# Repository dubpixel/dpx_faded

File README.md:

<!-- Improved compatibility of back to top link: See: https://github.com/othneildrew/Best-README-Template/pull/73 -->

<!--  *** Thanks for checking out the Best-README-Template. If you have a suggestion that would make this better, please fork the repo and create a pull request or simply open an issue with the tag "enhancement". Don't forget to give the project a star! Thanks again! Now go create something AMAZING! :D -->

<!-- /// d   u   b   p   i   x   e   l  ---  f   o   r   k   ////--v0.5.0 -->
<!--this has additionally been modifed by @dubpixel for hardware use -->
<!--search dpx_faded.. search & replace is COMMAND OPTION F -->

<!--todo add small product image thats not in a details tag -->
<!--igure out how to get the details tag to properly render in jekyll for gihub pages.-->

<!-- PROJECT SHIELDS -->
<!--
*** I'm using markdown "reference style" links for readability.
*** Reference links are enclosed in brackets [ ] instead of parentheses ( ).
*** See the bottom of this document for the declaration of the reference variables
*** for contributors-url, forks-url, etc. This is an optional, concise syntax you may use.
*** https://www.markdownguide.org/basic-syntax/#reference-style-links
***
-->
[![Contributors][contributors-shield]][contributors-url]
[![Forks][forks-shield]][forks-url]
[![Stargazers][stars-shield]][stars-url]
[![Issues][issues-shield]][issues-url]
[![CERN-OHL-S-2.0][license-shield]][license-url]
[![LinkedIn][linkedin-shield]][linkedin-url]

<!-- PROJECT LOGO -->
<br />
<div align="center">

<h1 align="center">dpx_faded</h1>
<h3 align="center"><i>because whats life without fader?</i></h3>
<br />
  <p align="center">
    ...a motorized fader breakout inspired by the FADER_4. Since there were only gerbers that didnt seem to match any faders available easily  - i re made a KiCAD project based on the 1.8 board revision. Included here for quick reference is a VScode migrated FADER_X firmware distro... soon to be migrated to its own _genuine_ fork.
        <br />
     »  
     <a href="https://github.com/dubpixel/dpx_faded/tree/main/"><strong>Project Here!</strong></a>
     »  
    <a href="https://github.com/dubpixel/dpx_faded/tree/main/hardware/src/dpx_faded/bom"><strong>BOM Here!</strong></a>
     » 
    <a href="https://dubpixel.github.io/dpx_faded/ibom/index.html"><strong>Interactive BOM Here!</strong></a>
     <br />
    <a href="https://github.com/dubpixel/dpx_faded/issues/new?labels=bug&template=bug-report---.md">Report Bug</a>
    ·
    <a href="https://github.com/dubpixel/dpx_faded/issues/new?labels=enhancement&template=feature-request---.md">Request Feature</a>
    </p>
</div>
   <br />
<!-- TABLE OF CONTENTS -->
<details>
<summary><h3>Table of Content</h3></summary>
<ol>
    <li>
      <a href="#about-the-project">About The Project</a>
      <ul>
        <li><a href="#built-with">Built With</a></li>
      </ul>
    </li>
    <li>
      <a href="#getting-started">Getting Started</a>
      <ul>
        <li><a href="#prerequisites">Prerequisites</a></li>
        <li><a href="#installation">Installation</a></li>
      </ul>
    </li>
    <li><a href="#usage">Usage</a></li>    
    <li><a href="#reflection">Reflection</a></li>
    <li><a href="#roadmap">Roadmap</a></li>
    <li><a href="#contributing">Contributing</a></li>
    <li><a href="#license">License</a></li>
    <li><a href="#contact">Contact</a></li>
    <li><a href="#acknowledgments">Acknowledgments</a></li>
</ol>
</details>
<br />
<!-- ABOUT THE PROJECT -->

<details>
<summary><h3>About The Project</h3></summary>
While the maker made the firmware open source, as well as the production gerber files - the cad files were not released in a malliable format, which doesnt allow further development of that hardware platform. (bummer). Since there is some community interest in the product, here we attempt to reverse engineer the FADE_4 as a proof of concept before continuing with development
</br>
author(s): // www.dubpixel.tv  - i@dubpixel.tv | other authors
</br>
<h3>Images</h3>

### FRONT
![FRONT][product-front]

### REAR 
![REAR][product-rear]

### FRONT Rendering
![FRONT][product-front-rendering]

### REAR Rendering
![REAR][product-rear-rendering]

### iBOM PCB Front
![iBOM Front][product-pcbFront]

### iBOM PCB Rear
![iBOM Front][product-pcbRear]

</details>

<p align="right">(<a href="#readme-top">back to top</a>)</p>

### Built With 
 * [![KiCad][KiCad.org]][KiCad-url]
 * [![Fusion360][Fusion-360]][Autodesk-url]
 * [![FastLed][FastLed.io]][FastLed-url]

<!--
  
 * [![Fusion360][Fusion-360]][Autodesk-url]
 * [![Next][Next.js]][Next-url]
 * [![React][React.js]][React-url]
 * [![Vue][Vue.js]][Vue-url]
 * [![Angular][Angular.io]][Angular-url]
 * [![Svelte][Svelte.dev]][Svelte-url]
 * [![Laravel][Laravel.com]][Laravel-url]
 * [![Bootstrap][Bootstrap.com]][Bootstrap-url]
 * [![JQuery][JQuery.com]][JQuery-url]
 
-->
<p align="right">(<a href="#readme-top">back to top</a>)</p>

<!-- GETTING STARTED -->
## Getting Started

### Prerequisites

### Installation

<!--
1. Download...
2. Enjoy.
3. Repeat as Needed! -->

<p align="right">(<a href="#readme-top">back to top</a>)</p>

<!-- USAGE EXAMPLES -->
## Usage

<!-- Use this space to show useful examples of how a project can be used. Additional screenshots, code examples and demos work well in this space. You may also link to more resources.

_For more examples, please refer to the [Documentation](https://example.com)_-->

<p align="right">(<a href="#readme-top">back to top</a>)</p>

## Reflection

* what did we learn? 
  - things take what they take. (good) things take more.
  - pinouts. always read the pinouts with parts on somoene elses BOM/hardware design
* what do we like/hate?
  - faders
  - the pinout from the fade 4 was kinda wack in the way that it forced me to do certain routing.
  - finally got the chance to do an on-the-board rj45 /  differential trace matching etc.
* what would/could we do differently?
 - wiper pin up top /  better routing of the analog pins, better use of the multilayer pcb

<!-- 
* what did we learn? 
* what do we like/hate?
* what would/could we do differently? 
-->

<p align="right">(<a href="#readme-top">back to top</a>)</p>

<!-- ROADMAP -->

## Roadmap

- [x] Reverse Enineer FADE_4 from gerber and firmware.
- [x] Re-Draw Front Panel
- [ ] Prove Existing FADE_4 Redesign 
    - [ ] with x32 faders
- [ ] Find source of touch faders from anyone but Apai
    - [ ] talking to lyric made me want to go be a dirt farmer
- [ ] Implement Touch sensors on faders
- [ ] Add additional control sets
  - [ ] X/y joystick
  - [ ] potentiometer
    - [ ] analog multiplexor for addtl analog ins
  - [ ] rotary encoder ?
  - [ ] adressable led
  - [ ] cherry keys / keymatrix

See the [open issues](https://github.com/dubpixel/dpx_faded/issues) for a full list of proposed features (and known issues).

<p align="right">(<a href="#readme-top">back to top</a>)</p>

<!-- CONTRIBUTING -->
## Contributing

Contributions are what make the open source community such an amazing place to learn, inspire, and create. Any contributions you make are **greatly appreciated**.

If you have a suggestion that would make this better, please fork the repo and create a pull request. You can also simply open an issue with the tag "enhancement".
Don't forget to give the project a star! Thanks again!

1. Fork the Project
2. Create your Feature Branch (`git checkout -b feature/AmazingFeature`)
3. Commit your Changes (`git commit -m 'Add some AmazingFeature'`)
4. Push to the Branch (`git push origin feature/AmazingFeature`)
5. Open a Pull Request

<p align="right">(<a href="#readme-top">back to top</a>)</p>

### Top contributors:

<!-- LICENSE -->
## License

  Distributed under the CERN Open Hardware Licence Version 2 - Strongly Reciprocal (CERN-OHL-S v2). See [`LICENSE`](LICENSE) for more information.

<p align="right">(<a href="#readme-top">back to top</a>)</p>

<!-- CONTACT -->
## Contact

  ### Joshua Fleitell - i@dubpixel.tv

  Project Link: [https://github.com/dubpixel/dpx_faded](https://github.com/dubpixel/dpx_faded)

<p align="right">(<a href="#readme-top">back to top</a>)</p>

<!-- ACKNOWLEDGMENTS -->
## Acknowledgments

* [stagehacks](https://github.com/stagehacks/FADER_X) - fader X project

<!--
  * [ ]() - the best 
-->

<p align="right">(<a href="#readme-top">back to top</a>)</p>

<!-- MARKDOWN LINKS & IMAGES -->
<!-- https://www.markdownguide.org/basic-syntax/#reference-style-links -->
[contributors-shield]: https://img.shields.io/github/contributors/dubpixel/dpx_faded.svg?style=for-the-badge
[contributors-url]: https://github.com/dubpixel/dpx_faded/graphs/contributors
[forks-shield]: https://img.shields.io/github/forks/gdubpixel/dpx_faded.svg?style=for-the-badge
[forks-url]: https://github.com/dubpixel/dpx_faded/network/members
[stars-shield]: https://img.shields.io/github/stars/dubpixel/dpx_faded.svg?style=for-the-badge
[stars-url]: https://github.com/dubpixel/dpx_faded/stargazers
[issues-shield]: https://img.shields.io/github/issues/dubpixel/dpx_faded.svg?style=for-the-badge
[issues-url]: https://github.com/dubpixel/dpx_faded/issues
[license-shield]: https://img.shields.io/badge/license-CERN--OHL--S--2.0-blue?style=for-the-badge
[license-url]: https://github.com/dubpixel/dpx_faded/blob/main/LICENSE
[linkedin-shield]: https://img.shields.io/badge/-LinkedIn-black.svg?style=for-the-badge&logo=linkedin&colorB=555
[linkedin-url]: https://linkedin.com/in/jfleitell
[product-front]: images/front.png
[product-rear]: images/rear.png
[product-front-rendering]: images/front_render.png
[product-rear-rendering]: images/rear_render.png
[product-pcbFront]: images/pcb_front.png
[product-pcbRear]: images/pcb_rear.png
[Next.js]: https://img.shields.io/badge/next.js-000000?style=for-the-badge&logo=nextdotjs&logoColor=white
[Next-url]: https://nextjs.org/
[React.js]: https://img.shields.io/badge/React-20232A?style=for-the-badge&logo=react&logoColor=61DAFB
[React-url]: https://reactjs.org/
[Vue.js]: https://img.shields.io/badge/Vue.js-35495E?style=for-the-badge&logo=vuedotjs&logoColor=4FC08D
[Vue-url]: https://vuejs.org/
[Angular.io]: https://img.shields.io/badge/Angular-DD0031?style=for-the-badge&logo=angular&logoColor=white
[Angular-url]: https://angular.io/
[Svelte.dev]: https://img.shields.io/badge/Svelte-4A4A55?style=for-the-badge&logo=svelte&logoColor=FF3E00
[Svelte-url]: https://svelte.dev/
[Laravel.com]: https://img.shields.io/badge/Laravel-FF2D20?style=for-the-badge&logo=laravel&logoColor=white
[Laravel-url]: https://laravel.com
[Bootstrap.com]: https://img.shields.io/badge/Bootstrap-563D7C?style=for-the-badge&logo=bootstrap&logoColor=white
[Bootstrap-url]: https://getbootstrap.com
[JQuery.com]: https://img.shields.io/badge/jQuery-0769AD?style=for-the-badge&logo=jquery&logoColor=white
[JQuery-url]: https://jquery.com 
[KiCad.org]: https://img.shields.io/badge/KiCad-v8.0.6-blue
[KiCad-url]: https://kicad.org 
[Fusion-360]: https://img.shields.io/badge/Fusion360-v4.2.0-green
[Autodesk-url]: https://autodesk.com 
[FastLed.io]: https://img.shields.io/badge/FastLED-v3.9.9-red
[FastLed-url]: https://fastled.io

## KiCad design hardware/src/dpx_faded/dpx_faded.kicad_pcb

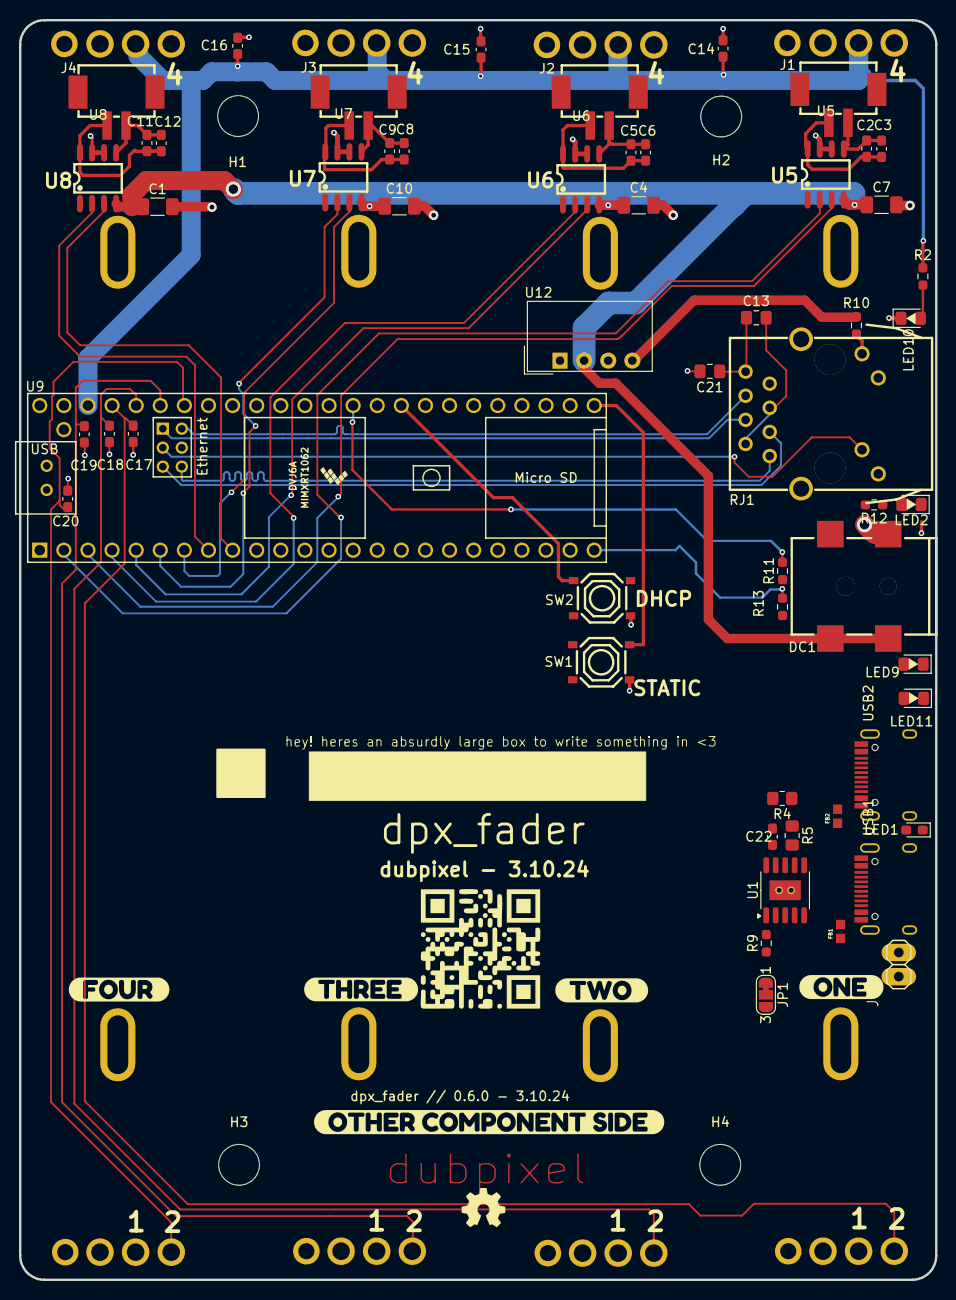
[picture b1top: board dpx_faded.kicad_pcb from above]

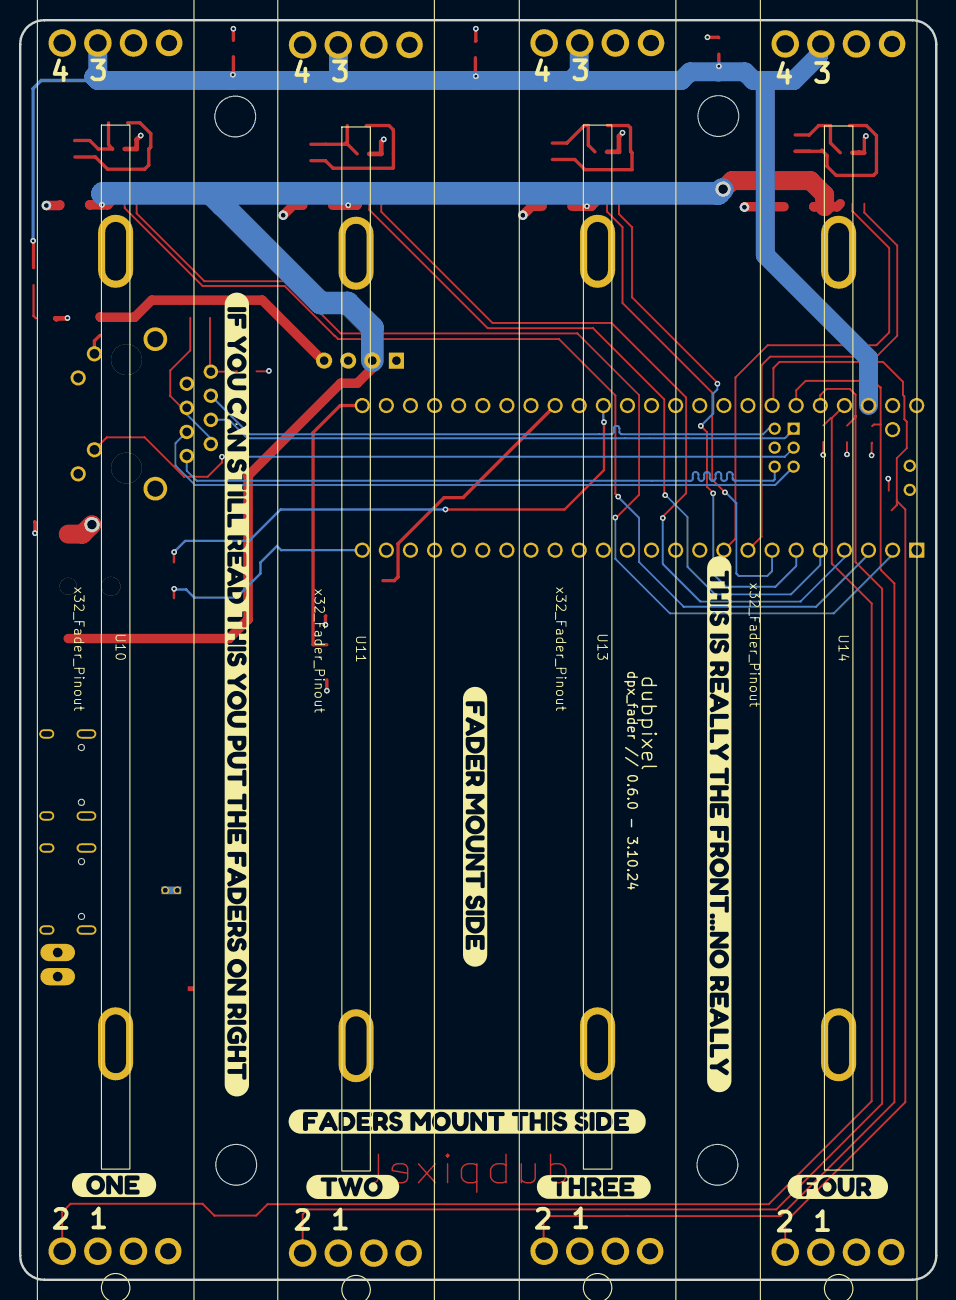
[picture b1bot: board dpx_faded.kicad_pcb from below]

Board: 4 copper layers, 96.5 x 132.7 mm, 78 parts (12 on the bottom side), 56 nets.

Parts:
C1, C4, C7, C10: 4.7 uF; C_1206_3216Metric_Pad1.33x1.80mm_HandSolder
C2, C3, C5, C6, C8, C9, C11, C12, C14, C15, C16, C17, C18, C19, C20: 100 NF; C_0603_1608Metric_Pad1.08x0.95mm_HandSolder
C13, C21: 100 nF; C_0805_2012Metric_Pad1.18x1.45mm_HandSolder
C22: 1 uF; C_0603_1608Metric_Pad1.08x0.95mm_HandSolder
DC1: DC-005-5A-2.0-SMT; DC-IN-TH_DC-005-5A-2.0-SMT
FB1, FB2: 220h 110mHz; FERRITE_0603
H1, H2, H3, H4: MountingHole_Pad_MP; MountingHole_4.3mm_M4_ISO14580
J1: motor.1; CONN-SMD_PH2.0-1X2PW
J2: motor.2; CONN-SMD_PH2.0-1X2PW
J3: motor.3; CONN-SMD_PH2.0-1X2PW
J4: motor.4; CONN-SMD_PH2.0-1X2PW
J5: Conn_01x02_Pin; 1X02
JP1: Jumper_3_Bridged12; SolderJumper-3_P1.3mm_Bridged12_RoundedPad1.0x1.5mm_NumberL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
LED1: RED; LED_0603_1608Metric_Pad1.05x0.95mm_HandSolder
LED2: GREEN; LED_0805_2012Metric_Pad1.15x1.40mm_HandSolder
LED9: RED; LED_0805_2012Metric_Pad1.15x1.40mm_HandSolder
LED10: YELLO; LED_0805_2012Metric_Pad1.15x1.40mm_HandSolder
LED11: WHITE; LED_0805_2012Metric_Pad1.15x1.40mm_HandSolder
R2: 65R; R_0603_1608Metric_Pad0.98x0.95mm_HandSolder
R4: 1k; R_0805_2012Metric_Pad1.20x1.40mm_HandSolder
R5: 10k; R_0805_2012Metric_Pad1.20x1.40mm_HandSolder
R9, R12, R13: 120R; R_0603_1608Metric_Pad0.98x0.95mm_HandSolder
R10: 680R; R_0603_1608Metric_Pad0.98x0.95mm_HandSolder
R11: 75R; R_0603_1608Metric_Pad0.98x0.95mm_HandSolder
RJ1: J1B1211CCD; RJ45-TH_J1B1211CCD
SW1, SW2: TS-1187A-B-A-B; SW-SMD_4P-L5.1-W5.1-P3.70-LS6.5-TL_H1.5
SYM1: Logo_Open_Hardware_Small; OSHW-LogoNT_7.3x6mm_Silk
U1: CH224K; SSOP-10-1EP_3.9x4.9mm_P1mm_EP2.1x3.3mm_ThermalVias
U5, U6, U7, U8: TC118S; SOP-8_L4.9-W3.9-P1.27-LS6.0-BL
U9: Teensy4.1; Teensy41_less_pins
U10, U11, U13, U14: Fader_behringerx32_b10k_100mm
U12: NML0505SC
USB1, USB2: HRO-TYPE-C-31-M-12; HRO-TYPE-C-31-M-12-Assembly
kibuzzard-67C3BB4B: G***; kibuzzard-67C3BB4B
kibuzzard-67C38A3C: G***; kibuzzard-67C38A3C
kibuzzard-67C38B05: G***; kibuzzard-67C38B05
kibuzzard-67C38035, kibuzzard-67C38035#2: G***; kibuzzard-67C38035
kibuzzard-67C38056, kibuzzard-67C38056#2: G***; kibuzzard-67C38056
kibuzzard-67C38062, kibuzzard-67C38062#2: G***; kibuzzard-67C38062
kibuzzard-67C38072, kibuzzard-67C38072#2: G***; kibuzzard-67C38072
kibuzzard-67CFB29D: G***; kibuzzard-67CFB29D
kibuzzard-67D0F279: G***; kibuzzard-67D0F279

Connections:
13_SCK: R11.2, U9.35 (13_SCK_LED)
+3.3V: C14.1, C15.1, C16.1, R2.2, U9.46 (3V3), U10.3 (GND), U11.3 (GND), U13.3 (GND), U14.3 (GND)
+5v-CLEAN: R10.2, U9.48 (VIN), U12.4 (VOUT+)
+5v-DIRTY: C1.1, C4.1, C7.1, C10.1, DC1.1, U5.4 (VDD), U6.4 (VDD), U7.4 (VDD), U8.4 (VDD)
BUTTON1: SW2.1 (A), U9.33 (41_A17)
BUTTON2: SW1.2 (B), U9.25 (33_MCLK2)
CC1: U1.7 (CC1), USB1.4 (CC1), USB2.4 (CC1)
CC2: U1.6 (CC2), USB1.10 (CC2), USB2.10 (CC2)
D+: U1.4 (D+), USB1.6 (DP1), USB1.8 (DP2)
D+2: U9.67 (D+), USB2.6 (DP1), USB2.8 (DP2)
D-: U1.5 (D-), USB1.5 (DN2), USB1.7 (DN1)
D-2: U9.66 (D-), USB2.5 (DN2), USB2.7 (DN1)
GND: C1.2, C4.2, C7.2, C10.2, C14.2, C15.2, C16.2, C17.2, C18.2, C19.2, C20.2, C21.2, C22.2, DC1.2, FB1.2, FB2.2, J5.2, LED2.1 (C), LED9.1 (C), LED10.1 (C), LED11.1 (C), RJ1.9 (LLED-), RJ1.11 (RLED-), RJ1.13 (GND), RJ1.14 (GND), SW1.4 (D), SW2.4 (D), U1.11 (GND), U5.6 (AGND), U5.7 (PGND), U6.6 (AGND), U6.7 (PGND), U7.6 (AGND), U7.7 (PGND), U8.6 (AGND), U8.7 (PGND), U9.1 (GND), U9.34 (GND), U9.47 (GND), U9.64 (GND), U10.1 (VCC), U11.1 (VCC), U12.1 (VIN-), U12.3 (VOUT-), U13.1 (VCC), U14.1 (VCC), USB1.1 (GND), USB1.12 (GND), USB2.1 (GND), USB2.12 (GND)
LED6: R13.2, U9.24 (32_OUT1B)
LLED+: RJ1.10 (LLED+), U9.61 (LED)
unnamed: C13.1, RJ1.2, RJ1.5
unnamed: C13.2, C21.1, RJ1.8
unnamed: J5.1, JP1.3 (B)
unnamed: JP1.2 (C), U12.2 (VIN+)
unnamed: LED1.2 (A), R9.1
unnamed: LED2.2 (A), R12.1
unnamed: LED9.2 (A), R11.1
unnamed: LED10.2 (A), R2.1
unnamed: LED11.2 (A), R13.1
unnamed: R5.2, U1.8 (VBUS)
unnamed: FB1.1, USB1.13 (SHIELD)
unnamed: FB2.1, USB2.13 (SHIELD)
PG: LED1.1 (C), U1.10 (PG)
R+: RJ1.4, U9.60 (R+)
R-: RJ1.6, U9.65 (R-)
RLED+: R10.1, RJ1.12 (RLED+)
T+: RJ1.1, U9.63 (T+)
T-: RJ1.3, U9.62 (T-)
VBUS: JP1.1 (A), R4.1, R5.1, USB1.2 (VBUS), USB1.11 (VBUS)
VBUS_uC: U9.49 (VUSB), USB2.2 (VBUS), USB2.11 (VBUS)
VDD: C22.1, R4.2, R9.2, U1.1 (VDD), U1.9 (CFG1)
mc1.D: U5.3 (IN-B), U9.3 (1_TX1_CTX2_MISO1)
mc1.U: U5.2 (IN-A), U9.2 (0_RX1_CRX2_CS1)
mc2.D: U6.3 (IN-B), U9.5 (3_LRCLK2)
mc2.U: U6.2 (IN-A), U9.4 (2_OUT2)
mc3.D: U7.3 (IN-B), U9.7 (5_IN2)
mc3.U: U7.2 (IN-A), U9.6 (4_BCLK2)
mc4.D: U8.3 (IN-B), U9.9 (7_RX2_OUT1A)
mc4.U: U8.2 (IN-A), U9.8 (6_OUT1D)
motor.1-NEG: C2.2, C3.2, J1.2, U5.5 (OUTB)
motor.1-POS: C2.1, C3.1, J1.1, U5.8 (OUTA)
motor.2-NEG: C5.2, C6.2, J2.2, U6.5 (OUTB)
motor.2-POS: C5.1, C6.1, J2.1, U6.8 (OUTA)
motor.3-NEG: C8.2, C9.2, J3.2, U7.5 (OUTB)
motor.3-POS: C8.1, C9.1, J3.1, U7.8 (OUTA)
motor.4-NEG: C11.2, C12.2, J4.2, U8.5 (OUTB)
motor.4-POS: C11.1, C12.1, J4.1, U8.8 (OUTA)
wiper_1: C17.1, U9.45 (23_A9_CRX1_MCLK1), U10.2 (Wiper), U10.4
wiper_2: C18.1, U9.44 (22_A8_CTX1), U11.2 (Wiper), U11.4
wiper_3: C19.1, U9.43 (21_A7_RX5_BCLK1), U13.2 (Wiper), U13.4
wiper_4: C20.1, U9.42 (20_A6_TX5_LRCLK1), U14.2 (Wiper), U14.4

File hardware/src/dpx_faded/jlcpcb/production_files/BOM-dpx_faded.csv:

Comment,Designator,Footprint,LCSC,Quantity
100 NF,"C11,C12,C13,C14,C15,C16,C17,C18,C19,C2,C20,C21,C3,C5,C6,C8,C9",C_0603_1608Metric_Pad1.08x0.95mm_HandSolder,C14663,17
YELLO,LED11,LED_0805_2012Metric_Pad1.15x1.40mm_HandSolder,C2296,1
GREEN,LED10,LED_0805_2012Metric_Pad1.15x1.40mm_HandSolder,C2297,1
680R,"R1,R10,R2,R3",R_0603_1608Metric_Pad0.98x0.95mm_HandSolder,C23228,4
4.7 uF,"C1,C10,C4,C7",C_1206_3216Metric_Pad1.33x1.80mm_HandSolder,C29823,4
TS-1187A-B-A-B,"SW1,SW2",SW-SMD_4P-L5.1-W5.1-P3.70-LS6.5-TL_H1.5,C318884,2
DC-005-5A-2.0-SMT,DC1,DC-IN-TH_DC-005-5A-2.0-SMT,C319134,1
motor.1,"J1,J2,J3,J4",CONN-SMD_PH2.0-1X2PW,C64658,4
RED,LED9,LED_0805_2012Metric_Pad1.15x1.40mm_HandSolder,C84256,1
TC118S,"U5,U6,U7,U8",SOP-8_L4.9-W3.9-P1.27-LS6.0-BL,C88308,4
J1B1211CCD,RJ1,RJ45-TH_J1B1211CCD,C910371,1
NML0505SC,U12,NML0505SC,,1
Teensy4.1,U9,Teensy41_less_pins,,1
~,U14,Fader_behringerx32_b10k_100mm,,1
~,U11,Fader_behringerx32_b10k_100mm,,1
~,U10,Fader_behringerx32_b10k_100mm,,1
~,U13,Fader_behringerx32_b10k_100mm,,1

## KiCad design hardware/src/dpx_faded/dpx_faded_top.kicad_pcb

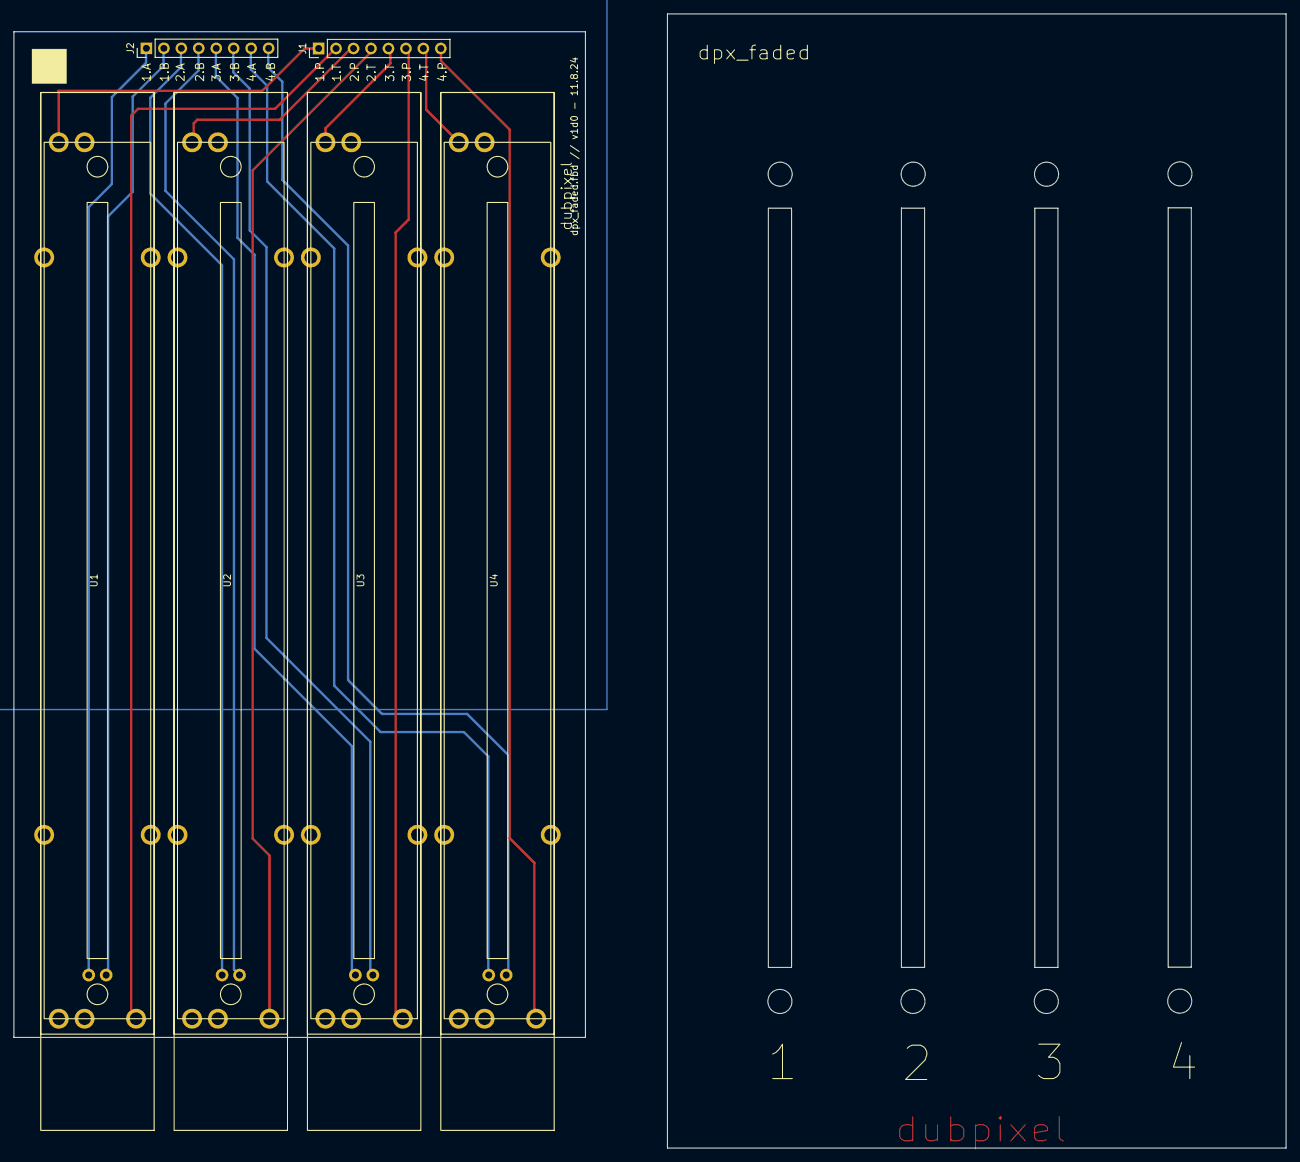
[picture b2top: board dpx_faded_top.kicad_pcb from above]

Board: 4 copper layers, 83.1 x 146.3 mm, 6 parts (0 on the bottom side), 18 nets.

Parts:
J1, J2: Conn_01x08_Pin; PinHeader_1x08_P2.54mm_Vertical
U1, U2, U3, U4: Fader_apai_SC1009M

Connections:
/M1_A: J2.1, U1.5 (+)
/M1_B: J2.2, U1.6 (-)
/M2_A: J2.3, U2.5 (+)
/M2_B: J2.4, U2.6 (-)
/M3_A: J2.5, U3.5 (+)
/M3_B: J2.6, U3.6 (-)
/M4_A: J2.7, U4.5 (+)
/M4_B: J2.8, U4.6 (-)
/P1: J1.1, U1.2 (Wiper)
/P2: J1.3, U2.2 (Wiper)
/P3: J1.5, U3.2 (Wiper)
/P4: J1.7, U4.2 (Wiper)
/T1: J1.2, U1.8 (Touch)
/T2: J1.4, U2.8 (Touch)
/T3: J1.6, U3.8 (Touch)
/T4: J1.8, U4.8 (Touch)
GND: U1.1 (VCC), U1.4 (GND), U2.1 (VCC), U2.4 (GND), U3.1 (VCC), U3.4 (GND), U4.1 (VCC), U4.4 (GND)
VCC: U1.3 (GND), U2.3 (GND), U3.3 (GND), U4.3 (GND)

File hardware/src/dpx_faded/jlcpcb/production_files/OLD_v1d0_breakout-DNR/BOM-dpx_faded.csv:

Comment,Designator,Footprint,LCSC
Conn_01x08_Pin,J2,PinHeader_1x08_P2.54mm_Vertical,
~,U2,Fader_apai_SC1009M,
~,U4,Fader_apai_SC1009M,
~,U3,Fader_apai_SC1009M,
~,U1,Fader_apai_SC1009M,
Conn_01x08_Pin,J1,PinHeader_1x08_P2.54mm_Vertical,

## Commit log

2024-11-13 images, mfg files, readme
    updated pcb renderings, files for mfg and the readme
2024-11-13 Update README.md
    i hate trying to format this and having to commit each time its ridiculous
2024-11-13 remove_reorg
2024-12-09 specsheets and such
    ignore a big file as well
2024-12-10 Create logo.png
    upload dpx logo
2024-12-16 pre-redesign push
2025-03-01 so much source and so much datasheet
    lots of fader drama
    gonna fork the design and reduce featureset, add x32 faders due to availa
    basically make a FADE_4 clone first because well - that whole thing has turned into the mystery project
2025-03-02 first release
    ** big reorganize
    ++ version 1.0 of FADED4_LYFE based on v1.8 of FADE4
    ++ lots of fader related spec sheets.
    --remove backup files and other erratta
2025-03-02 Update README.md
    ** fix link to bom directory
2025-03-02 bom rearrange + production files
    ** copy a bom to a place
    ++ added production files (even though i thought we had?)
2025-03-02 Update README.md
    ** take two on the bom pathj
2025-03-02 add template and theme files for readme and pages
    ++ issue tempate
    ++ feature request template
    ** copy the ibom to the folder for ibom
    ?? looks like page rendering may still be broken?
2025-03-02 ibom vs ebom
    i thought this made the last commit?
2025-03-02 hi did i mention im kindof an idiot?
    ibom vs index
2025-03-02 adding this gemfile and some edits to the readme
    ** hopefully this change will keep the comments from rendering
2025-03-02 Update README.md
    **maybe try this to get that last comment out?
    ** def need to backtrack all this stuff to the template
2025-03-02 Update README.md
    fun more readme pagnation
2025-03-02 gotta be sure to edit the .yml for the title in jekyll
2025-03-02 Update README.md
    table of contents not collapsing
2025-03-02 Update README.md
    maybe try this
2025-03-02 Update README.md
    second details somehow encapsulated everything?
2025-03-02 Update README.md
    ok...
2025-03-02 Update README.md
    try again
2025-03-03 panel files, rearrange most recent produciton files
    ++ front panel
    ** re-arrange production file
2025-03-04 update readme
    update readme
2025-03-04 schematic stuff
    ** cleanup schematic
    ++ 74HC4051 mux
    ++ 4x joysticks
2025-03-04 schematic
    ** clean up schematic
    ++ pdf of schematic
2025-03-05 dxf exports
2025-03-09 joysticks... but going back to the main branch to make some easier changes
2025-03-09 specs and cleaned up schematic
2025-03-11 something
2025-05-06 post v0.5.0 fixes--->(v0.6.0)
    -----//HARDWARE
    ++ CH244 PD controller rough in
    ++ update PCB
    ++ add pdf for a fader
    -----//FIRMWARE
    ++ add maxpatch to test faders
2025-05-06 firmware and hardware fixes
    -------//FIRMWARE
    ** changed static/reset ip to 10.0 values (see reset.ino&WebServerApply.Ino) 10.0.10.130 & sending to 10.0.10.120
    ++ added maxpatch to test midi / motor functionality
    ++ 3mf for the enclosure
    ------//HARDWARE
    ** corrected some LED pinout shiz, other stuff.
2026-03-18 refresh base files and push some pcb stuff
2026-03-18 remove firmware to move to new repo
2026-03-18 v0.7.0 — re-license to CERN-OHL-S v2
